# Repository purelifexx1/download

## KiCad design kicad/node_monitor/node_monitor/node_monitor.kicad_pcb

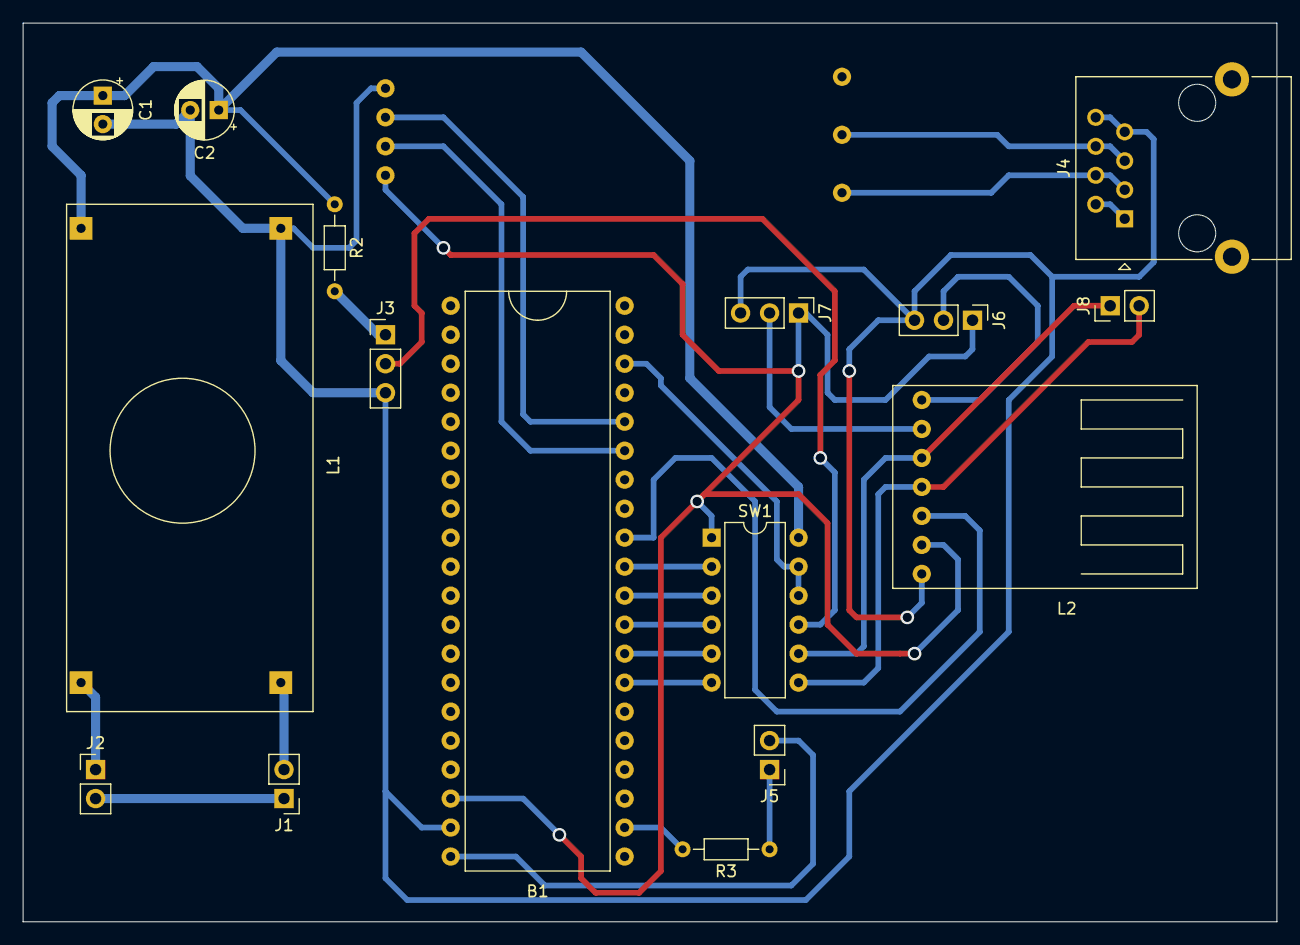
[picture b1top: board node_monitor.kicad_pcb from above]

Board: 2 copper layers, 109.9 x 78.7 mm, 17 parts (1 on the bottom side), 26 nets.

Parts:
B1: bluepill; BLUEPILL
C1: C; CP_Radial_D5.0mm_P2.50mm
C2: CP; CP_Radial_D5.0mm_P2.50mm
J1, J2, J5, J8: Conn_01x02_Male; PinHeader_1x02_P2.54mm_Vertical
J3, J6, J7: Conn_01x03_Male; PinHeader_1x03_P2.54mm_Vertical
J4: RJ45; RJ45_Ninigi_GE
L1: LM2596
L2: LORA
R1: RS485
R2, R3: R; R_Axial_DIN0204_L3.6mm_D1.6mm_P7.62mm_Horizontal
SW1: SW_DIP_x06; DIP-12_W7.62mm

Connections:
3V3: B1.20, B1.38, J5.2, SW1.10, SW1.11
A: J4.3, J4.4, R1.5
AUX: B1.32, L2.5
B: J4.5, J4.6, R1.6
GND1: B1.19, B1.40, C1.2, C2.2, J3.3, J4.7, J4.8, J6.3, J7.3, L1.4, L2.7, R1.4
LRXD: J8.1, L2.3, SW1.8
LRXI: B1.27, SW1.5
LTXD: J8.2, L2.4, SW1.7
LTXI: B1.28, SW1.6
M0: J6.2, L2.1
M1: J7.2, L2.2
MANUAL: B1.30, SW1.3
MODE: B1.31, SW1.2
unnamed: B1.22, R3.2
unnamed: J1.1, J2.2
unnamed: J1.2, L1.2
unnamed: J2.1, L1.1
unnamed: J3.1, R2.2
unnamed: J4.1, J4.2
unnamed: J5.1, R3.1
RLD: J3.2, SW1.9
RLI: B1.29, SW1.4
RRXD: B1.36, R1.3
RTXD: B1.35, R1.2
VCCI: B1.18, J6.1, J7.1, L2.6, R1.1, SW1.1
VCCO: C1.1, C2.1, L1.3, R2.1, SW1.12

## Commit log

2020-08-21 next
2020-08-22 nothing
2020-09-01 3333
2020-09-14 54548
2020-09-22 fefef
2020-09-24 4141
2020-09-27 123456
2020-09-28 1234
2020-10-14 6598
2020-10-16 5878
2020-10-26 3698
2020-10-30 132434
2020-12-07 3689
